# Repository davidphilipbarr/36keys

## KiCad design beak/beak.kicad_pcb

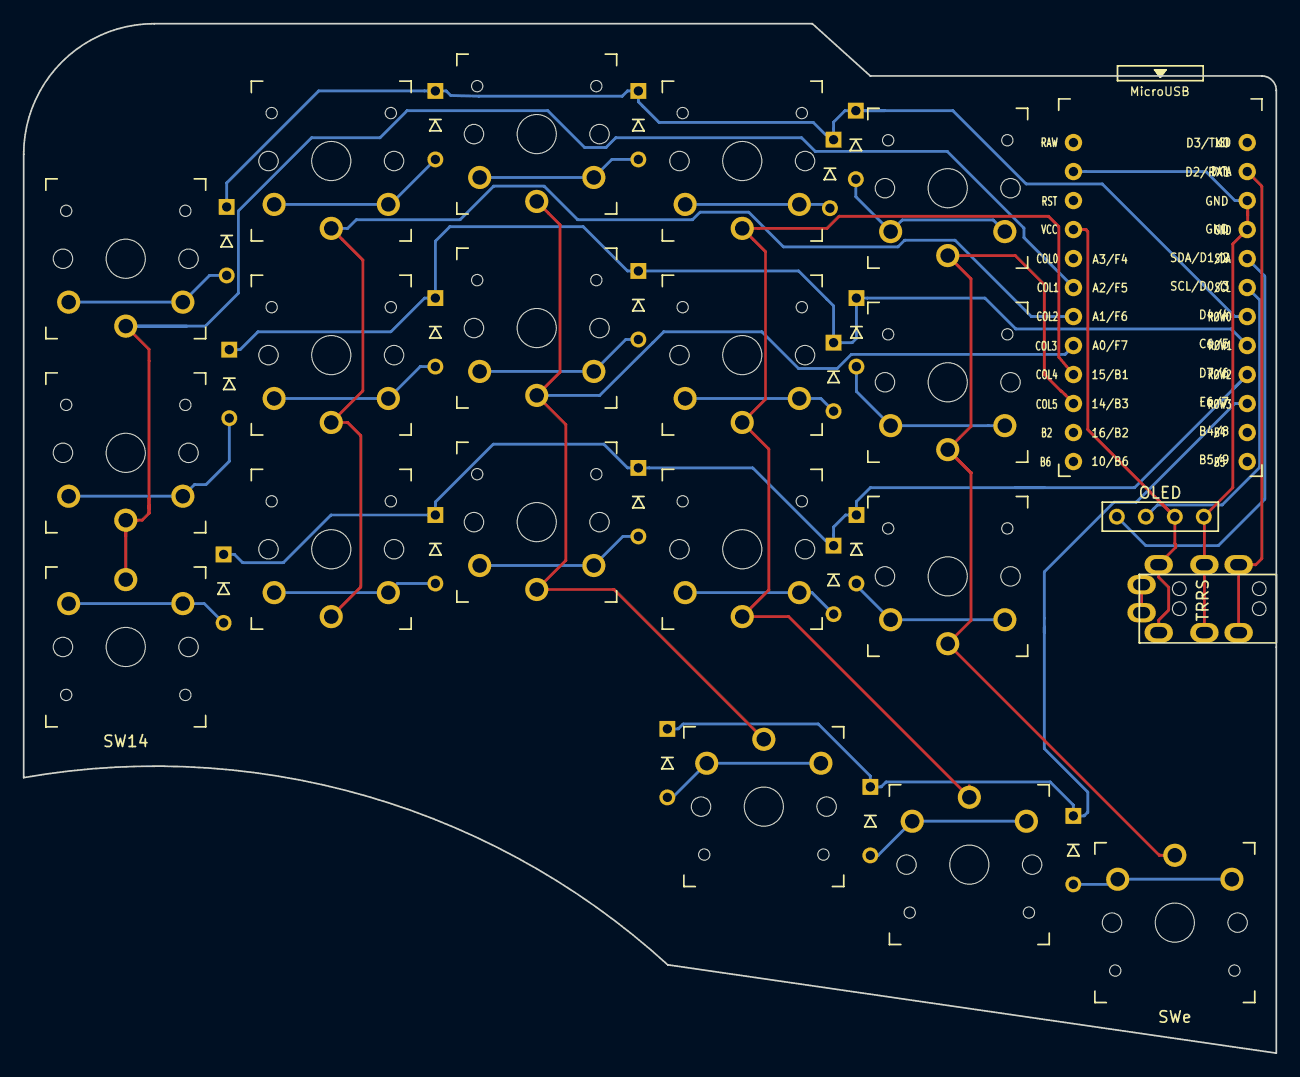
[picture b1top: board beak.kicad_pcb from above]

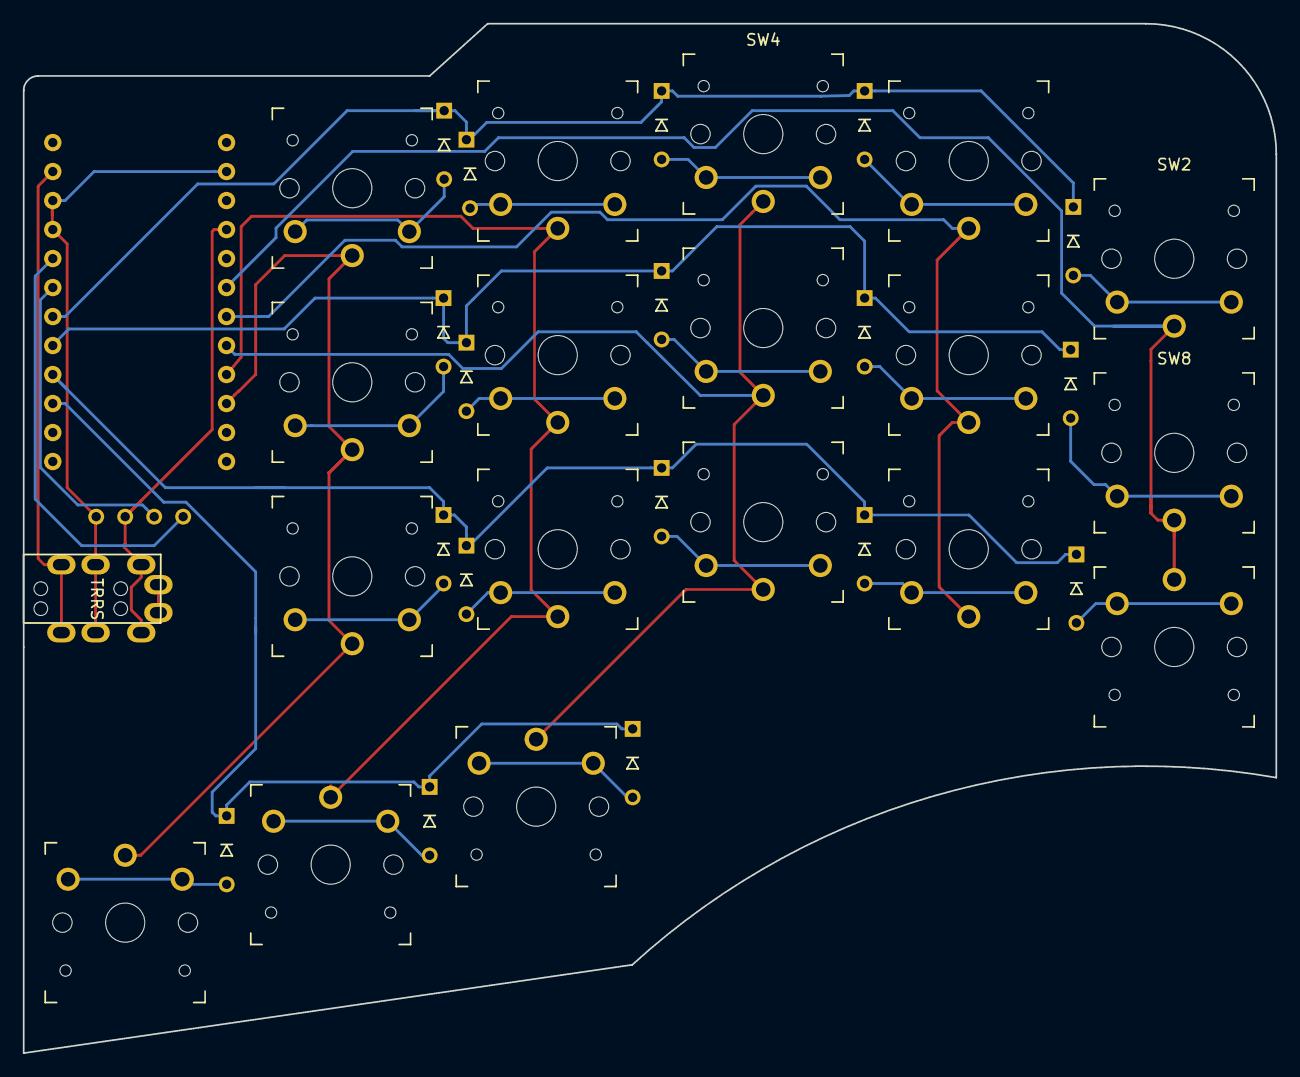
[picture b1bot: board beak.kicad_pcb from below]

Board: 2 copper layers, 109.7 x 90.2 mm, 39 parts (4 on the bottom side), 32 nets.

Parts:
D2, D3, D4, D5, D6, D8, D9, D10, D11, D12, D14, D15, D16, D17, D18, D19, D20, D21: D; D3_TH
J1: MJ-4PP-9
J2: OLED; OLED_1side
SW2, SW3, SW4, SW5, SW6, SW8, SW9, SW10, SW11, SW12, SW14, SW15, SW16, SW17, SW18, SW19, SW20: SW_PUSH; SW_PG1350_reversible
SWe: SW_PUSH; SW_PG1350_reversible
U1: ProMicro; ProMicro_v3

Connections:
GND: J1.C, J2.4, U1.3, U1.4, U1.23
unnamed: D2.2, SW2.2
unnamed: D3.2, SW3.2
unnamed: D4.2, SW4.2
unnamed: D5.2, SW5.2
unnamed: D6.2, SW6.2
unnamed: D8.2, SW8.2
unnamed: D9.2, SW9.2
unnamed: D10.2, SW10.2
unnamed: D11.2, SW11.2
unnamed: D12.2, SW12.2
unnamed: D14.2, SW14.2
unnamed: D15.2, SW15.2
unnamed: D16.2, SW16.2
unnamed: D17.2, SW17.2
unnamed: D18.2, SW18.2
unnamed: D19.2, SW19.2
unnamed: D20.2, SW20.2
unnamed: D21.2, SWe.2
SCL: J2.2, U1.6
SDA: J2.1, U1.5
VCC: J1.D, J2.3, U1.21
col1: SW2.1, SW8.1, SW14.1, U1.19
col2: SW3.1, SW9.1, SW15.1, U1.18
col3: SW4.1, SW10.1, SW16.1, SW19.1, U1.17
col4: SW5.1, SW11.1, SW17.1, SW20.1, U1.16
col5: SW6.1, SW12.1, SW18.1, SWe.1, U1.15
data: J1.B, U1.2
row0: D2.1, D3.1, D4.1, D5.1, D6.1, U1.7
row1: D8.1, D9.1, D10.1, D11.1, D12.1, U1.8
row2: D14.1, D15.1, D16.1, D17.1, D18.1, U1.9
row3: D19.1, D20.1, D21.1, U1.10

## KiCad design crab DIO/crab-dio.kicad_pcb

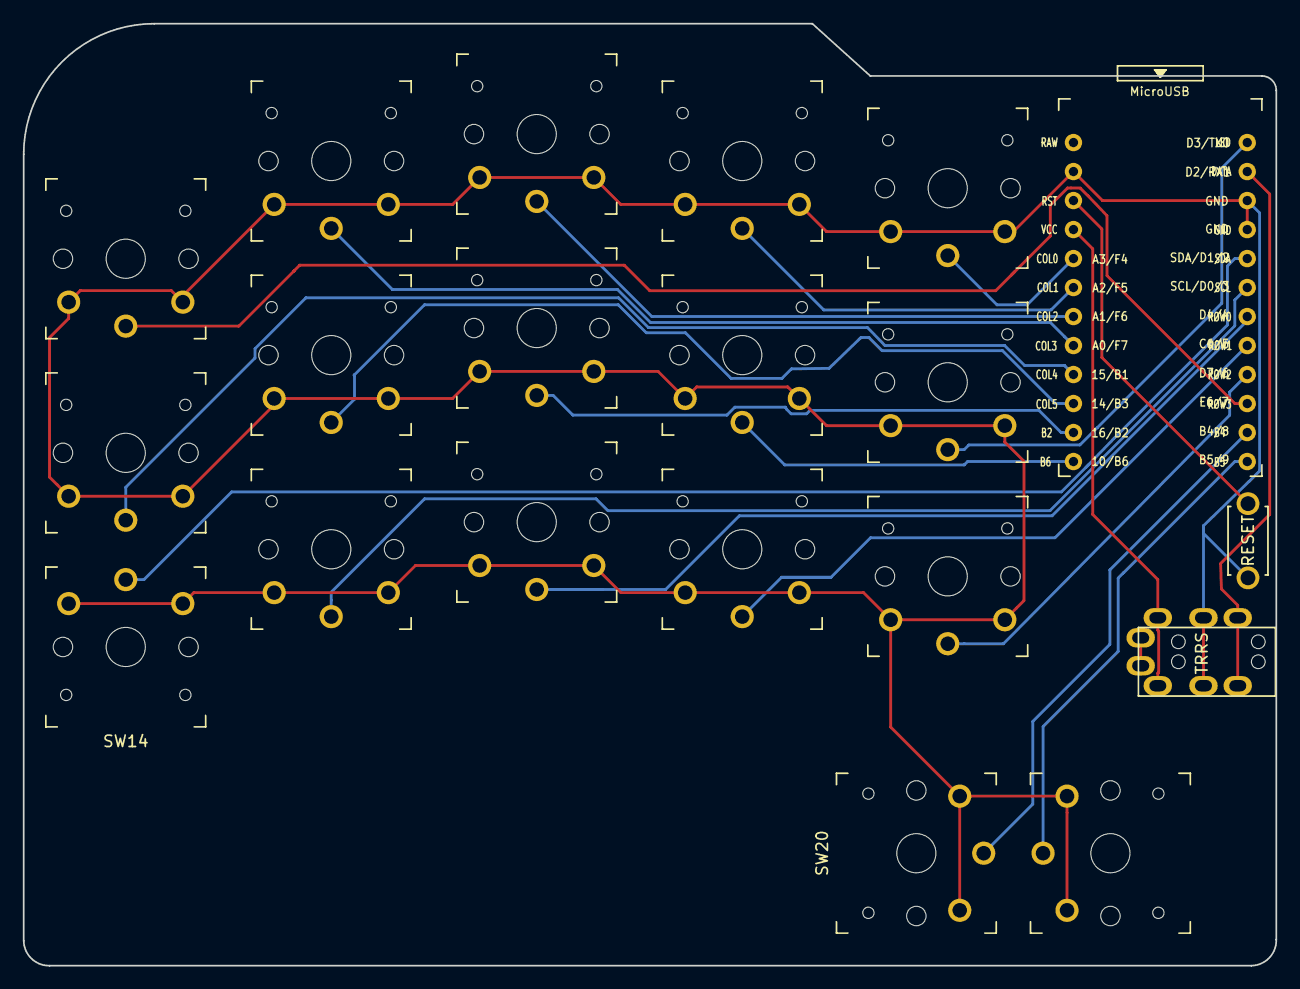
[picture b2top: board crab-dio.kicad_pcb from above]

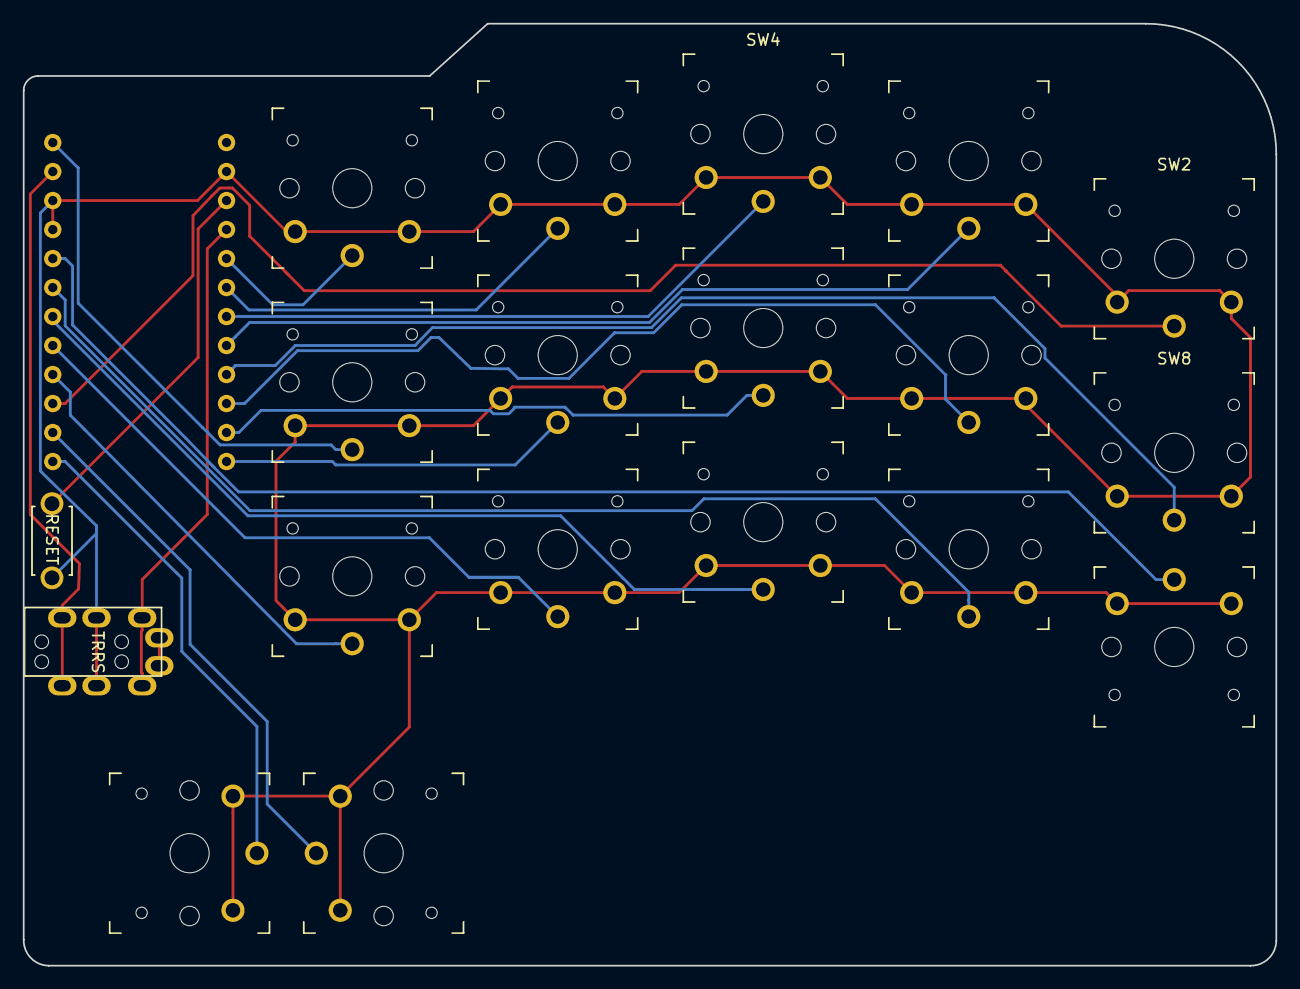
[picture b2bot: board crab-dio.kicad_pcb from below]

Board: 2 copper layers, 109.7 x 82.5 mm, 20 parts (3 on the bottom side), 21 nets.

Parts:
J1: MJ-4PP-9
RSW1: Val**; ResetSW
SW2, SW3, SW4, SW5, SW6, SW8, SW9, SW10, SW11, SW12, SW14, SW15, SW16, SW17, SW18, SW20, SW21: SW_PUSH; SW_PG1350_reversible
U1: ProMicro; ProMicro_v3

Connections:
GND: J1.C, RSW1.2, SW2.2, SW3.2, SW4.2, SW5.2, SW6.2, SW8.2, SW9.2, SW10.2, SW11.2, SW12.2, SW14.2, SW15.2, SW16.2, SW17.2, SW18.2, SW20.2, SW21.2, U1.3, U1.4, U1.23
LED: SW12.1, U1.1
unnamed: SW6.1, U1.20
unnamed: SW20.1, U1.11
unnamed: SW21.1, U1.12
unnamed: SW11.1, U1.13
unnamed: SW10.1, U1.14
SCL: SW15.1, U1.6
SDA: SW14.1, U1.5
VCC: J1.D, U1.21
col1: SW5.1, U1.19
col2: SW4.1, U1.18
col3: SW3.1, U1.17
col4: SW8.1, U1.16
col5: SW9.1, U1.15
data: J1.B, U1.2
reset: RSW1.1, U1.22
row0: SW16.1, U1.7
row1: SW17.1, U1.8
row2: SW18.1, U1.9
row3: SW2.1, U1.10
